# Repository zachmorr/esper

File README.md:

# This Project has moved!

It can now be [found here](https://github.com/openesper/esper).

This repo is just kept so history is still available

# About Esper

Heavily inspired by the [Pi-Hole](https://github.com/pi-hole/pi-hole), this project aims to bring network wide ad-blocking to another popular device popular among makers and hobbyists, the ESP32.

## What is DNS?

Commonly referred to as the "phone book for the internet", the DNS protocol is how devices map human readable urls like google.com or facebook.com into IP addresses that the device can use.

## How does Esper block ads?

Just like the [Pi-Hole](https://github.com/pi-hole/pi-hole), Esper acts as a DNS server for devices. When sent a DNS query, Esper will read the url the device is requesting, then decide to block the request by returning 0.0.0.0 or forward the request on to a real DNS server.

## Differences between Pi-hole and Esper

The biggest, and most obvious difference is the hardware these projects run on. Pi-hole aims to be available on any Linux powered hardware, while Esper is an ESP32 specific project. Due to being run on a microcontroller, Esper is much more limited in it's capabilities and is therefore much more minimal in it's design.

## Why choose Esper instead of Pi-hole?

Choose whatever one suits you! If you like tinkering with hardware, and do not have much experience with the Raspberry Pi/Linux ecosystem, setting up the Esper software on an ESP32 dev board might be an interesting project. And while Esper may not be nearly as powerful as a Raspberry Pi, DNS protocol is very lightweight in nature. Unless you are in a household with 10+ people that are always online you will likely never going to need more computing power than a microcontroller can provide.

At the same time, if you have no problem using a shell and Linux environment, the Pi-hole is a much more feature rich and powerful piece of software that is a joy to use.

## How can I get an Esper?

The easiest way, is to purchase a pre-made one from the Tindie store. (Link incoming...) 

If you have some ESP32 development boards collecting dust, it will work on those too! It will take some slight configuration ([see instructions here](https://github.com/zachmorr/esper/blob/main/software/README.md)), but you can have it running in no time.

DISCLAIMER: It is **heavily** recommended to use a device with ethernet. Even the best Wifi will significantly increase latency and decrease reliability compared to a good copper connection.

If you want to try you hand an making an Esper from scratch, the hardware directory contains all the schematic, pcb, and enclosure files needed to build one yourself.

## Reprogramming Esper

Do you like the Esper hardware, but want to use it for something other than ad-blocking? Great! The Esper hardware is completely reprogrammable and includes an on-board USB-UART converter, no extra programmers are needed!

# Esper Development

## Tools Used

* KiCAD	- EDA tool used to design PCB
* FreeCAD - 3D modeling tool for designing enclosure
* Hugo - Static website generator used for embedded Esper website
* ESP-IDF - Contains ESP32 API and build tools for firmware development
* Python 3.7 - Scripts to glue everything together

## Directory Structure

    ├── hardware                    # Hardware root directory
    │   ├── custom components           # Custom KiCad component files
    │   ├── enclosure                   # FreeCAD project and STL files for enclosure
    │   ├── product                     # KiCad projects for Esper
    │   │   ├── usb-programmable        	# Includes CP2102 for easy usb programming
    │   │   └── jtag-header             	# 10-pin header for JTAG & UART, meant to be used with programmer
    │   └── programmer                  # KiCad project for programmer/debugger
    └── software                    # Software root directory
        ├── default blacklist           # List of URLs that will be blocked by default
        ├── firmware                    # ESP-IDF project that contains all code for Esper
        ├── scripts                     # Scripts used in build process and testing
        ├── tests                       # Scripts used in testing (not started yet)
        └── website                     # Hugo project used to generate website

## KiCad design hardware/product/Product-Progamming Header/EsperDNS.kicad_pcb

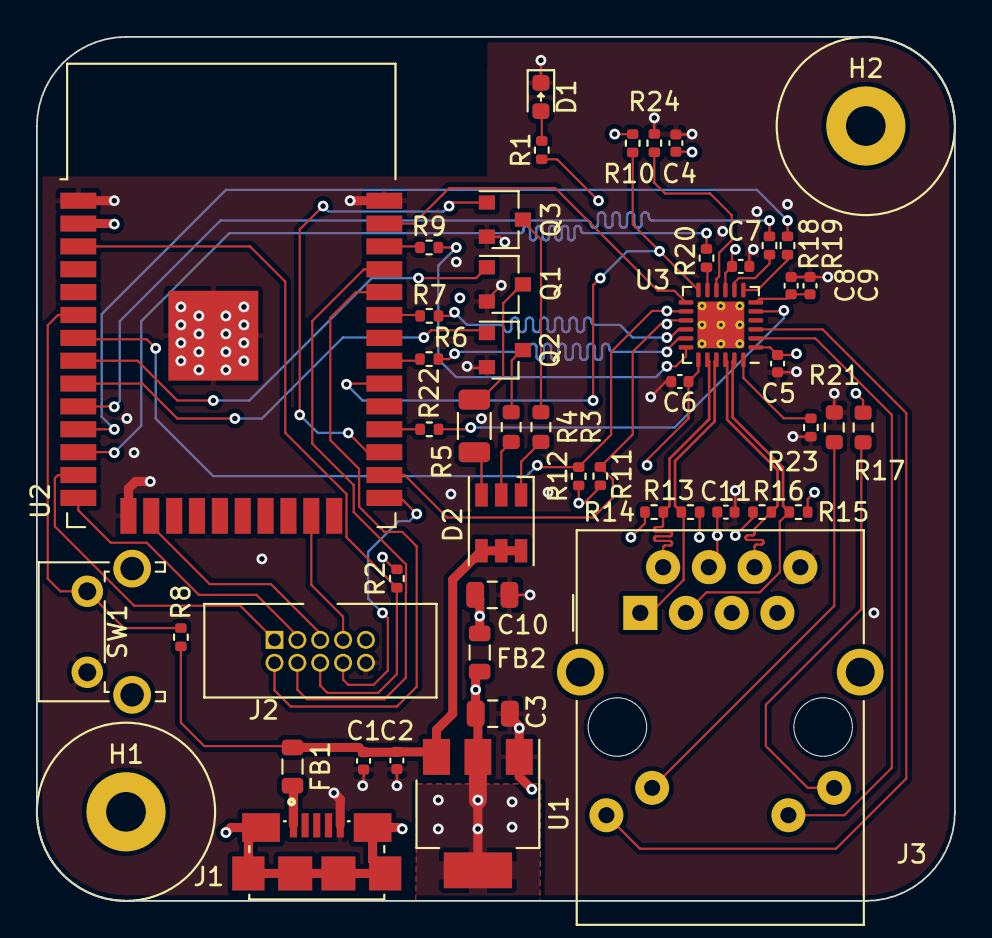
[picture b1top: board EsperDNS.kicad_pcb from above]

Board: 4 copper layers, 51.0 x 48.0 mm, 51 parts (0 on the bottom side), 54 nets.

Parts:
C1, C4, C9: 1uF; C_0402_1005Metric
C2, C5, C6, C7, C8, C11: 0.1uF; C_0402_1005Metric
C3, C10: 10uF; C_0805_2012Metric
D1: GRN; D_0603_1608Metric
D2: RS-3535MWAR; LED_RGB_PLCC-6
FB1, FB2: Ferrite_Bead; L_0805_2012Metric
H1, H2: MountingHole; MountingHole_2.2mm_M2_Pad
J1: 10118192-0001LF; AMPHENOL_10118192-0001LF
J2: Conn_02x05_Odd_Even; CNC_3220-10-0100-00
J3: RJ45_Amphenol_RJMG1BD3B8K1ANR
Q1, Q2, Q3: 2N7002; SOT-23
R1: 470; R_0402_1005Metric
R2, R8, R10, R11, R12, R24: 10K; R_0402_1005Metric
R3, R4: 47; R_0603_1608Metric
R5: 82; R_1206_3216Metric
R6, R7, R9, R13, R14, R15, R16, R18, R19, R20, R22: 49.9; R_0402_1005Metric
R17, R21: 270; R_0603_1608Metric
R23: 12.1K; R_0402_1005Metric
SW1: PTS645VH83-2 LFS; SW_Tactile_SPST_Angled_PTS645Vx83-2LFS
U1: AZ1117EH-3.3TRG1; SOT-223
U2: ESP32-WROOM-32E; ESP32-WROOM-32
U3: LAN8720A; QFN-24-1EP_4x4mm_P0.5mm_EP2.6x2.6mm_ThermalVias

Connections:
+3.3VA: C4.1, C5.1, C6.1, C10.1, C11.1, FB2.1, J3.R4, J3.R5, R10.1, R11.1, R12.1, R13.1, R14.1, R15.1, R16.1, R17.1, U3.1, U3.19
+3V3: C3.1, C7.1, FB2.2, R1.1, R2.2, U1.2, U1.4, U2.2, U3.9
/ESP32/CLK_R: R22.2, U2.28
/ESP32/TXD0_R: R6.1, U2.31
/ESP32/TXD1_R: R9.1, U2.36
/ESP32/TXEN_R: R7.1, U2.33
/Ethernet/CRS_DV_R: R20.1, U3.11
/Ethernet/LEDG_K: J3.L3, R21.1
/Ethernet/LEDY_A: J3.L1, R17.2
/Ethernet/PHYAD0: R24.1, U3.10
/Ethernet/RBIAS: R23.1, U3.24
/Ethernet/RD+: J3.R3, R15.2, U3.23
/Ethernet/RD-: J3.R6, R16.2, U3.22
/Ethernet/RX0_R: R18.1, U3.8
/Ethernet/RX1_R: R19.1, U3.7
/Ethernet/TD+: J3.R1, R13.2, U3.21
/Ethernet/TD-: J3.R2, R14.2, U3.20
Block: R8.2, SW1.2, U2.6
Blue: Q3.1, U2.27
CLK50MHZ: R22.1, U3.5
CRS_DV: R20.2, U2.12
EN: J2.6, R2.1, U2.3
Earth: H1.1, H2.1, J1.6, J3.13
GND: C1.2, C2.2, C3.2, C4.2, C5.2, C6.2, C7.2, C8.2, C9.2, C10.2, C11.2, D1.1, J1.5, J2.10, J3.R8, Q1.2, Q2.2, Q3.2, R21.2, R23.2, R24.2, SW1.1, U1.1, U2.1, U2.15, U2.38, U2.39, U3.25
Green: Q2.1, U2.9
IO0: J2.8, U2.25
LED1_REGOFF: J3.L4, U3.3
LED2_nINTSEL: J3.L2, U3.2
MDC: U2.37, U3.13
MDIO: R10.2, U2.30, U3.12
MTCK: J2.5, U2.16
MTDI: J2.3, U2.14
MTDO: J2.7, U2.23
MTMS: J2.1, U2.13
unnamed: D1.2, R1.2
unnamed: D2.1, R3.1
unnamed: D2.2, R4.1
unnamed: D2.3, R5.1
unnamed: FB1.2, J1.1
unnamed: Q1.3, R5.2
unnamed: Q2.3, R4.2
unnamed: Q3.3, R3.2
RX: J2.4, U2.35
RXD0: R18.2, U2.10
RXD1: R19.2, U2.11
Red: Q1.1, U2.8
TX: J2.2, U2.34
TXD0: R6.2, U3.17
TXD1: R9.2, U3.18
TXEN: R7.2, U3.16
VBUS: C1.1, C2.1, D2.4, D2.5, D2.6, FB1.1, R8.1, U1.3
VDDCR: C8.1, C9.1, U3.6
nINT: R12.2, U2.7, U3.14
nRST: R11.2, U2.26, U3.15

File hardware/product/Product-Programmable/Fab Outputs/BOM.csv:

Comment,Designator,Footprint,LCSC
"1uF","C1,C4,C9,C12","Capacitor_SMD:C_0402_1005Metric","C52923"
"10uF","C3,C10","Capacitor_SMD:C_0805_2012Metric","C15850"
"0.1uF","C2,C5,C6,C7,C8,C11","Capacitor_SMD:C_0402_1005Metric","C1525"
"GRN","D1","Diode_SMD:D_0603_1608Metric","C72043"
"RS-3535MWAR","D2","LED_SMD:LED_RGB_PLCC-6"," C110402"
"Ferrite_Bead","FB2","Inductor_SMD:L_0805_2012Metric","C1015"
"MountingHole","H1,H2","MountingHole:MountingHole_2.2mm_M2_Pad",""
"USB_B_Micro","J1","Connector_USB:USB_Micro-B_Molex-105017-0001",""
"RJ45_Amphenol_RJMG1BD3B8K1ANR","J3","Connector_RJ:RJ45_Amphenol_RJMG1BD3B8K1ANR",""
"2N7002","Q1,Q2,Q3,Q4,Q5","Package_TO_SOT_SMD:SOT-23","C8545"
"470","R1","Resistor_SMD:R_0402_1005Metric"," C25117"
"10K","R2,R8,R10,R11,R12,R24","Resistor_SMD:R_0402_1005Metric","C25744"
"270","R17,R21","Resistor_SMD:R_0603_1608Metric","C22966"
"12.1K","R23","Resistor_SMD:R_0402_1005Metric","C25852"
"47","R3,R4","Resistor_SMD:R_0603_1608Metric","C23182"
"82","R5","Resistor_SMD:R_1206_3216Metric","C247183"
"49.9","R6,R7,R9,R13,R14,R15,R16,R18,R19,R20,R22","Resistor_SMD:R_0402_1005Metric","C25120"
"PTS645VH83-2 LFS","SW1","Button_Switch_THT:SW_Tactile_SPST_Angled_PTS645Vx83-2LFS",""
"AZ1117EH-3.3TRG1","U1","Package_TO_SOT_SMD:SOT-223","C108494"
"ESP32-WROOM-32E","U2","RF_Module:ESP32-WROOM-32","C701341"
"LAN8720A","U3","Package_DFN_QFN:QFN-24-1EP_4x4mm_P0.5mm_EP2.6x2.6mm_ThermalVias","C45223"
"CP2102-GMR_NRND","U4","EsperFootprints:VFQFN-28-1EP_5x5mm",""

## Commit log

2021-01-24 Combined all repos into one
2021-01-24 Changed build scripts and file organization to work with monorepo
2021-01-25 Fixed some bugs in website
2021-01-26 Removed gcode
2021-01-26 Removed lines from .gitignore
2021-01-26 Changed project name
2021-02-10 Updated webserver to use JSON, and ota over http
2021-02-10 Fixed blocking button
2021-02-10 Removed sdkconfig
2021-02-10 Removed ota version check
2021-02-10 Added sdkconfig back to repo
2021-02-10 Test commit
2021-02-10 Testing update version checking
2021-02-10 Testing update version checking pt2
2021-02-10 pt49
2021-02-20 Started on ota diagnostics
2021-02-22 Add menuconfig configuration options to support dev boards
2021-02-23 refactoring flash.c
2021-02-23 Still working on configuration options, also added error component
2021-02-23 I dunno
2021-02-24 Figuring out how to refactor wifi
2021-02-24 Slowly making progress...
2021-02-24 STA mode successfully connects
2021-02-25 Working in ap mode
2021-02-25 Fixed conflict with accesspoint.c
2021-02-25 Integrating new netif files with the rest of the application
2021-02-26 Moved to using global event groups
2021-02-26 Finished move over to new netif component, added new event component
2021-03-01 Still refactoring
2021-03-04 Small update
2021-03-05 small reoraganization
2021-03-06 Finished and tested DNS
2021-03-07 Starting up GPIO/LED stuff
2021-03-13 Finished first version of GPIO
2021-03-13 Initial version of OTA working
2021-03-14 More OTA work done, added more error catching
2021-03-16 Minor housekeeping
2021-03-16 Adding more OTA capability to website
2021-03-17 Close to feature complete, need to add documentation and run through tests
2021-03-17 Fixed mistakes in ToDo.md
2021-03-17 Changed some permissions and updated build script
2021-03-17 Started writing down tests that need doing
2021-03-26 Added more error handling to DNS, no more receive buffer errors
2021-03-29 Added more README
2021-03-30 Added more documentation
2021-03-30 Adding more documentation
2021-04-02 Even more documentation
2021-04-04 Fixed bug in auto-programming circuit by adding 1uf cap on EN
2021-04-05 Small changes
2021-04-05 Added build scripts for Windows
2021-04-05 Updated schematic to be more readable
2021-04-06 Gitignore changes
2021-04-06 Renaming some stuff
2021-04-06 Added fab outputs for usb esper
2021-04-06 Hardware readme
2021-04-09 Created PDFs of schematics, updates to documentation
2021-04-09 Final Commit
